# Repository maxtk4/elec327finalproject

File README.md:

# ELEC 327 Final Project

Written to run on a custom PCB with an MSPM0G3507 through code composer studio. There is another README.txt file in the code repository which explains the code better.

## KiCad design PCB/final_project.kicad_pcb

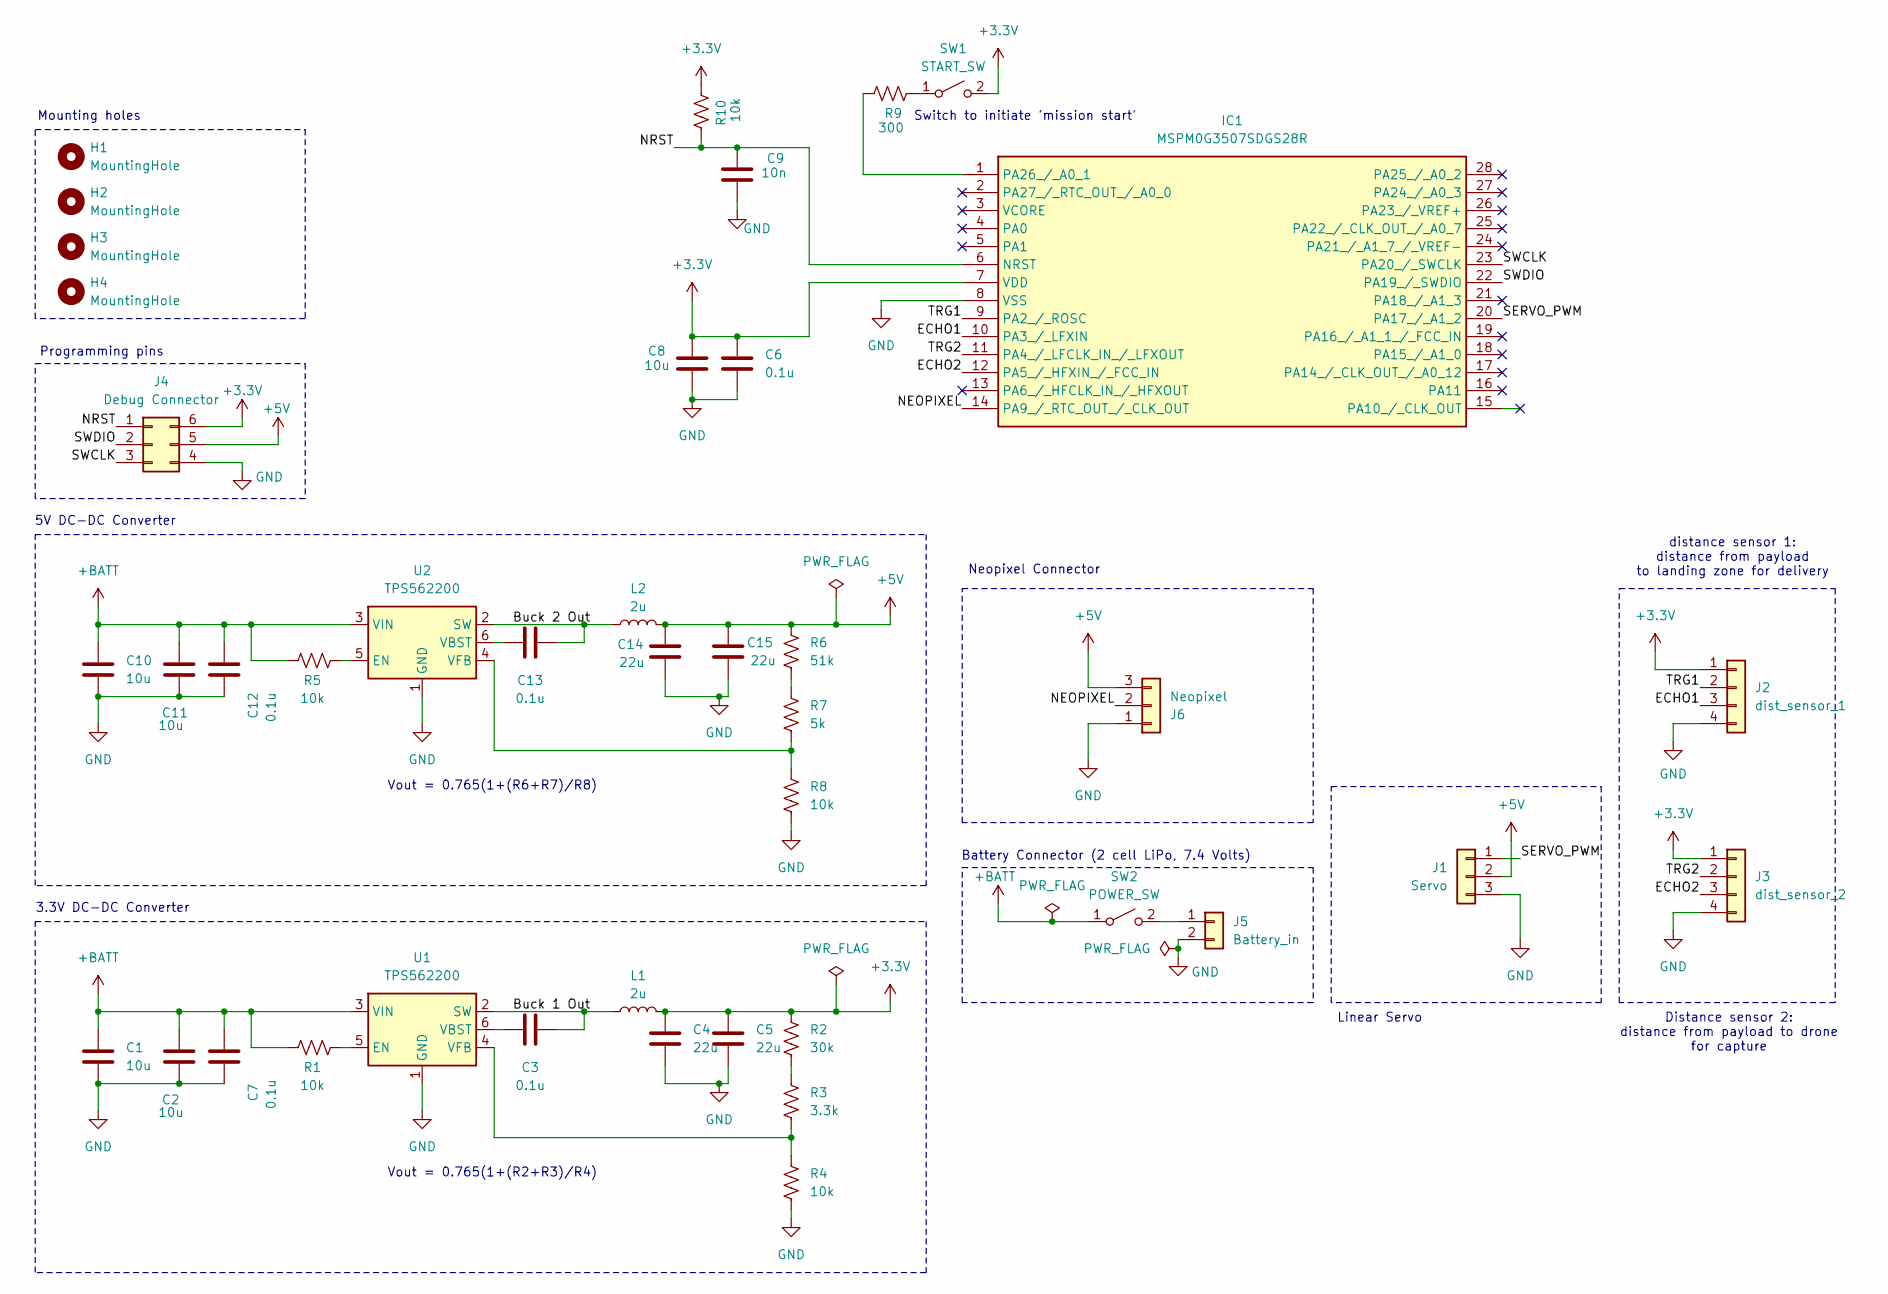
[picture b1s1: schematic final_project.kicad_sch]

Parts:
C1, C2, C10, C11: 10u; C_0805_2012Metric; LCSC C1691
C3, C6, C7, C12, C13: 0.1u; C_0805_2012Metric; LCSC C1525
C4, C5, C14, C15: 22u; C_0805_2012Metric; LCSC C12891
C8: 10u; C_0805_2012Metric; LCSC C1525
C9: 10n; C_0805_2012Metric; LCSC C1525
H1, H2, H3, H4: MountingHole; MountingHole_2.2mm_M2
IC1: MSPM0G3507SDGS28R; VSSOP28_DGS_TEX; Mouser Part Number 595-MSPM0G3107SDG28R
J1: Servo; PinHeader_1x03_P2.54mm_Vertical
J2: dist_sensor_1; PinHeader_1x04_P2.54mm_Vertical
J3: dist_sensor_2; PinHeader_1x04_P2.54mm_Vertical
J4: Debug Connector; PinHeader_2x03_P2.54mm_Vertical
J5: Battery_in; AMASS_XT30U-M_1x02_P5.0mm_Vertical
J6: Neopixel; PinHeader_1x03_P2.54mm_Vertical
L1, L2: 2u; L_Sunlord_SWPA8040S
R1, R4, R5, R8, R10: 10k; R_0805_2012Metric
R2: 30k; R_0805_2012Metric
R3: 3.3k; R_0805_2012Metric
R6: 51k; R_0805_2012Metric
R7: 5k; R_0805_2012Metric
R9: 300; R_0805_2012Metric
SW1: START_SW; PinHeader_1x02_P2.54mm_Vertical
SW2: POWER_SW; PinHeader_1x02_P2.54mm_Vertical
U1, U2: TPS562200; SOT-23-6

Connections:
+3.3V: C4.2, C5.2, C6.1, C8.1, IC1.7 (VDD), J2.1, J3.1, J4.6, L1.2, R2.1, R10.2, SW1.2 (B)
+5V: C14.2, C15.2, J1.2, J4.5, J6.3, L2.2, R6.1
+BATT: C1.1, C2.1, C7.2, C10.1, C11.1, C12.2, R1.1, R5.1, SW2.1 (A), U1.3 (VIN), U2.3 (VIN)
/Buck 1 Out: C3.2, L1.1, U1.2 (SW)
/Buck 2 Out: C13.2, L2.1, U2.2 (SW)
/ECHO1: IC1.10 (PA3_/_LFXIN), J2.3
/ECHO2: IC1.12 (PA5_/_HFXIN_/_FCC_IN), J3.3
/NEOPIXEL: IC1.14 (PA9_/_RTC_OUT_/_CLK_OUT), J6.2
/NRST: C9.1, IC1.6 (NRST), J4.1, R10.1
/SERVO_PWM: IC1.20 (PA17_/_A1_2), J1.1
/SWCLK: IC1.23 (PA20_/_SWCLK), J4.3
/SWDIO: IC1.22 (PA19_/_SWDIO), J4.2
/TRG1: IC1.9 (PA2_/_ROSC), J2.2
/TRG2: IC1.11 (PA4_/_LFCLK_IN_/_LFXOUT), J3.2
GND: C1.2, C2.2, C4.1, C5.1, C6.2, C7.1, C8.2, C9.2, C10.2, C11.2, C12.1, C14.1, C15.1, IC1.8 (VSS), J1.3, J2.4, J3.4, J4.4, J5.2, J6.1, R4.2, R8.2, U1.1 (GND), U2.1 (GND)
unnamed: IC1.1 (PA26_/_A0_1), R9.1
unnamed: J5.1, SW2.2 (B)
unnamed: R2.2, R3.1
unnamed: R6.2, R7.1
unnamed: R9.2, SW1.1 (A)
unnamed: R1.2, U1.5 (EN)
unnamed: C3.1, U1.6 (VBST)
unnamed: R3.2, R4.1, U1.4 (VFB)
unnamed: R5.2, U2.5 (EN)
unnamed: C13.1, U2.6 (VBST)
unnamed: R7.2, R8.1, U2.4 (VFB)

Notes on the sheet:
Vout = 0.765(1+(R2+R3)/R4)
Linear Servo
distance sensor 1: distance from payload to landing zone for delivery
Mounting holes
Battery Connector (2 cell LiPo, 7.4 Volts)
Neopixel Connector
Switch to initiate 'mission start'
Vout = 0.765(1+(R6+R7)/R8)
Distance sensor 2: distance from payload to drone for capture
5V DC-DC Converter
Programming pins
3.3V DC-DC Converter

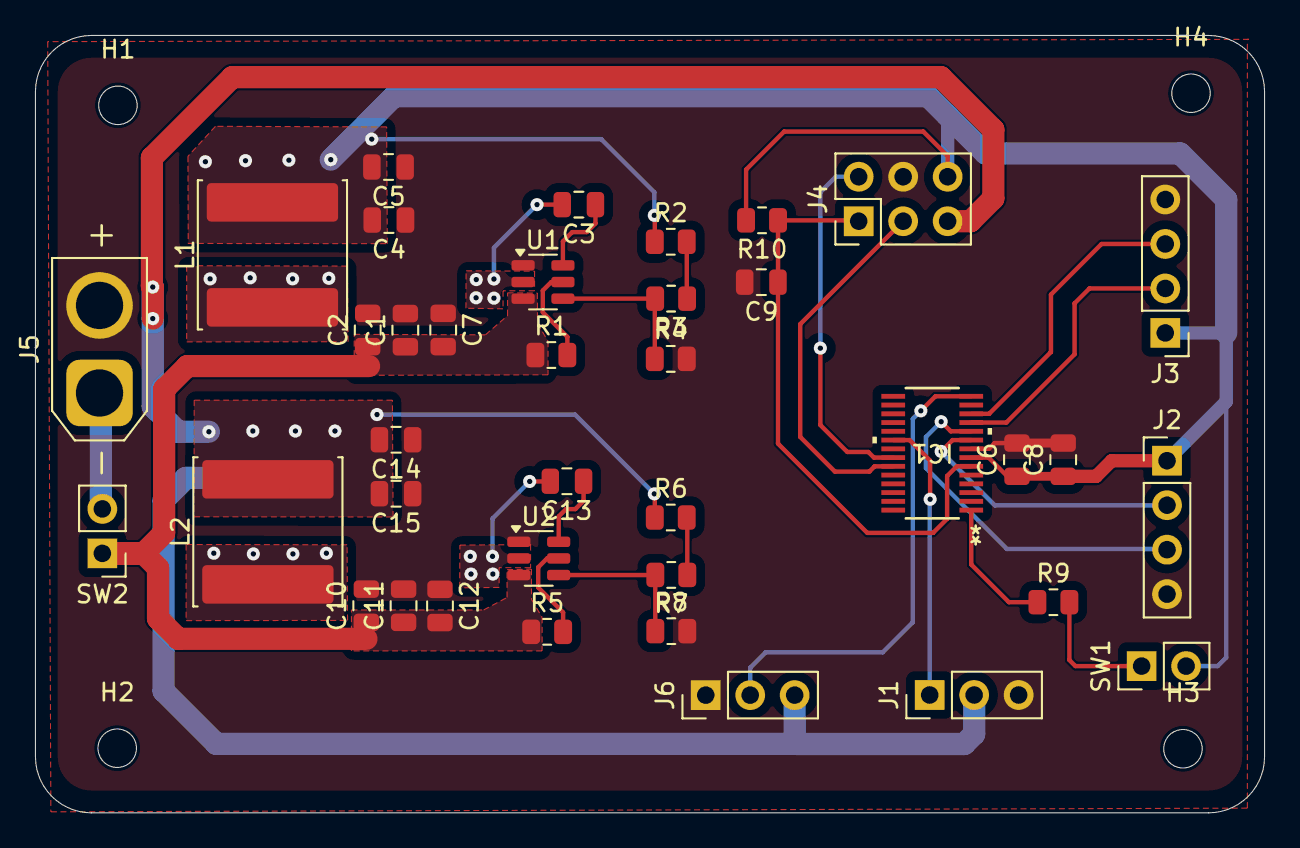
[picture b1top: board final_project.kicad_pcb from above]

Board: 4 copper layers, 70.2 x 44.4 mm, 42 parts (0 on the bottom side), 26 nets.

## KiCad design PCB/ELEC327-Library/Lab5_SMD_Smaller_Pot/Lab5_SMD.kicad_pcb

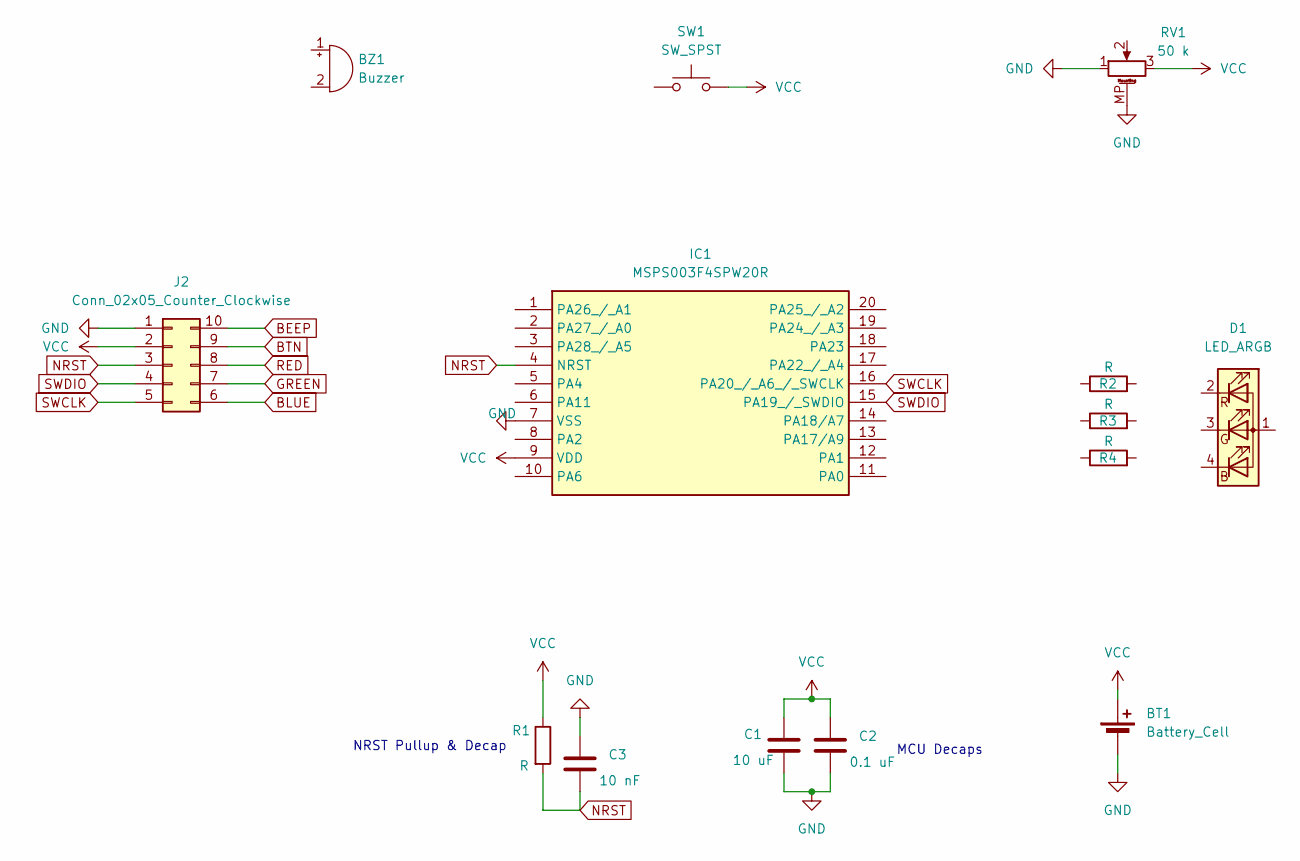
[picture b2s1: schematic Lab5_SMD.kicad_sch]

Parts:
BT1: Battery_Cell; BatteryHolder_Keystone_1060_1x2032
BZ1: Buzzer; Buzzer_Murata_PKMCS0909E
C1: 10 uF; C_1210_3225Metric_Pad1.33x2.70mm_HandSolder
C2: 0.1 uF; C_0805_2012Metric_Pad1.18x1.45mm_HandSolder
C3: 10 nF; C_0805_2012Metric_Pad1.18x1.45mm_HandSolder
D1: LED_ARGB; LED_RGB_1210
IC1: MSPS003F4SPW20R; TSSOP-20_4.4x6.5mm_P0.65mm; Mouser Part Number 595-MSPS003F4SPW20R
J2: Conn_02x05_Counter_Clockwise; PinHeader_2x05_P2.54mm_Vertical
R1, R2, R3, R4: R; R_0805_2012Metric_Pad1.20x1.40mm_HandSolder
RV1: 50 k; Potentiometer_Alps_RK09K_Single_Vertical
SW1: SW_SPST; SW_SPST_PTS645

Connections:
BEEP: J2.10
BLUE: J2.6
BTN: J2.9
GND: BT1.2 (-), C1.2, C2.2, C3.1, IC1.7 (VSS), J2.1, RV1.1, RV1.MP (MountPin)
GREEN: J2.7
NRST: C3.2, IC1.4 (NRST), J2.3, R1.2
RED: J2.8
SWCLK: IC1.16 (PA20_/_A6_/_SWCLK), J2.5
SWDIO: IC1.15 (PA19_/_SWDIO), J2.4
VCC: BT1.1 (+), C1.1, C2.1, IC1.9 (VDD), J2.2, R1.1, RV1.3, SW1.2

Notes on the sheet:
MCU Decaps
NRST Pullup & Decap

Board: 2 copper layers, 14 parts (0 on the bottom side), 5 nets, no tracks yet.

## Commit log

2025-05-13 Initial Commit'
2025-05-13 Making website
2025-05-14 Moving website files
2025-05-14 Fixing website
2025-05-14 Fleshing out website
2025-05-14 Adding PCB
2025-05-14 Adding second video
